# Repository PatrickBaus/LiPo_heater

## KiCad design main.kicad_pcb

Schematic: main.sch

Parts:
J1: USB_MICRO
J2, J3: Conn_01x02; JST_PH_B2B-PH-K_02x2.00mm_Straight
LOGO1: Logo_Open_Hardware_Small; OSHW-Logo_7.5x8mm_SilkScreen
Q1: DMP1045U; SOT-23
R1: 10k; R_0603_1608Metric

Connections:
/BAT+: J2.1; also elsewhere on the board
/Microcontroller/~enable_heater: Q1.1, R1.2; also elsewhere on the board
/Power Supply/V+5: Q1.2, R1.1; also elsewhere on the board
/Power Supply/VUSB: J1.1; also elsewhere on the board
GND: J1.5, J1.6, J2.2, J3.2; also elsewhere on the board
unnamed: J3.1, Q1.3

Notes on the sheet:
Heater

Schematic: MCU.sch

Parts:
C10, C11, C12: 100n; C_0603_1608Metric
J6: Conn_01x02; JST_PH_B2B-PH-K_02x2.00mm_Straight
J7: AVR-ISP-6; PinHeader_2x03_P2.54mm_Vertical
Q3: MMBT3904; SOT-23
R13: 1k; R_0603_1608Metric
R14, R17, R18: 4.7k; R_0603_1608Metric
R15: 470; R_0603_1608Metric
R16: 10k; R_0603_1608Metric
SW2: SW_SPDT; SW_CuK_OS102011MA1QN1_SPDT_Angled
U4: ATtiny13-20SSU; SOIC-8_3.9x4.9mm_P1.27mm

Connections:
/BAT+: R13.2; also elsewhere on the board
/Microcontroller/MISO: J7.1, R18.2, U4.6 (PB1)
/Microcontroller/MOSI: J7.4, R17.2, U4.5 (PB0)
/Microcontroller/RST: J7.5, R16.2, U4.1 (~RESET~/PB5)
/Microcontroller/SCK: J7.3, R14.2, U4.7 (PB2)
/Microcontroller/~enable_heater: U4.2 (PB3); also elsewhere on the board
/Power Supply/V+5: C10.1, J7.2, R15.1, R16.1, U4.8 (VCC); also elsewhere on the board
/Power Supply/~Kill_power: R17.1; also elsewhere on the board
GND: C10.2, C11.2, C12.2, J7.6, Q3.2 (E), SW2.1, U4.4 (GND); also elsewhere on the board
unnamed: C11.1, R13.1, U4.3 (PB4)
unnamed: C12.1, R14.1, SW2.2
unnamed: J6.1, R15.2
unnamed: J6.2, Q3.3 (C)
unnamed: Q3.1 (B), R18.1

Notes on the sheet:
To program the arduino. Connect the following wires: GND -> Pin 6 CTS -> Not Connected 5V/3.3V -> Pin 2 TXD ->
We are using a transistor so that we can isolate the pin using a 4.7k resistor

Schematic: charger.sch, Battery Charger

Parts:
C1, C2: 10u; C_0805_2012Metric
D1: Red LED; LED_0805_2012Metric
D2: Green LED; LED_0805_2012Metric
R2: 470; R_0603_1608Metric
R3: 1k; R_0603_1608Metric
R4: 2k; R_0603_1608Metric
U1: MCP73831; SOT-23-5

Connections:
/BAT+: C2.1, U1.3; also elsewhere on the board
/Power Supply/VUSB: C1.1, R2.2, U1.4; also elsewhere on the board
GND: C1.2, C2.2, R3.1, R4.1, U1.2; also elsewhere on the board
unnamed: D1.1, D2.2, U1.1
unnamed: D1.2, R2.1
unnamed: D2.1, R3.2
unnamed: R4.2, U1.5

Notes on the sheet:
Turns on, when fully charged
Turns on, when the charger is connected

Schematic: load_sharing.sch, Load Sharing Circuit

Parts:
Q2: NTLJF3117P; DFN-6-2EP_2x2mm_Pitch0.65mm
R5: 100k; R_0603_1608Metric

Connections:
/BAT+: Q2.3, Q2.8; also elsewhere on the board
/Power Supply/DC/DC boost converter/Vsup: Q2.4, Q2.6, Q2.7; also elsewhere on the board
/Power Supply/VUSB: Q2.1, Q2.5, R5.1; also elsewhere on the board
GND: R5.2; also elsewhere on the board

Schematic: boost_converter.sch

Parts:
C3: 10n; C_0603_1608Metric
C4, C8, C9: 47u; C_0805_2012Metric
C5: 100n; C_0603_1608Metric
C6: 200p; C_0603_1608Metric
C7: 18p; C_0603_1608Metric
D3: LED; LED_0805_2012Metric
JP1, JP2: SolderJumper_2_Open; SolderJumper-2_P1.3mm_Open_RoundedPad1.0x1.5mm
L1: 22u; Coilcraft_MSS7341
R6, R19: 1k; R_0603_1608Metric
R7: 100k; R_0603_1608Metric
R8: 332k; R_0603_1608Metric
R9: 33k; R_0603_1608Metric
R10: 150k; R_0603_1608Metric
R11: 22.6k; R_0603_1608Metric
R12: 1.1M; R_0603_1608Metric
SW1: SW_Push; SW_Tactile_SPST_Angled_PTS645Vx31-2LFS
TP1: Test_Point; TestPoint_Pad_D1.5mm
U2: LTC2955-1(DFN); DFN-10-1EP_2x3mm_P0.5mm_EP0.64x2.4mm
U3: LTC3536; DFN-10-1EP_3x3mm_P0.5mm_EP1.55x2.48mm

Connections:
/Power Supply/DC/DC boost converter/Vsup: C4.1, JP1.1, R6.1, U3.7; also elsewhere on the board
/Power Supply/V+5: C8.1, C9.1, JP2.1, R11.1, R12.1, R19.1, TP1.1, U3.6; also elsewhere on the board
/Power Supply/~Kill_power: JP2.2, U2.9; also elsewhere on the board
GND: C3.2, C4.2, C5.2, C8.2, C9.2, D3.1, R7.2, R8.2, R10.2, SW1.1, U2.6, U2.7, U2.10, U3.2, U3.3, U3.11; also elsewhere on the board
unnamed: C3.1, R6.2, U2.4
unnamed: C5.1, U2.8
unnamed: C6.1, R9.1
unnamed: C6.2, C7.2, R10.1, R12.2, U3.9
unnamed: C7.1, R11.2
unnamed: D3.2, R19.2
unnamed: JP1.2, R7.1, U2.3, U3.8
unnamed: L1.1, U3.4
unnamed: L1.2, U3.5
unnamed: R8.1, U3.1
unnamed: R9.2, U3.10
unnamed: SW1.2, U2.5

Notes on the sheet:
5.2 seconds/μF + 64 ms until forced shutdown
332 kΩ ≜ 300 kHz
Optional: Close JP1 for debugging to always enable the DC/DC converter
Optional: Close JP2 for debugging to keep the DC/DC converter enabled
The LTC2955 requires only 1.2 µA of current so the 1k resistor is OK and it allows reverse input.

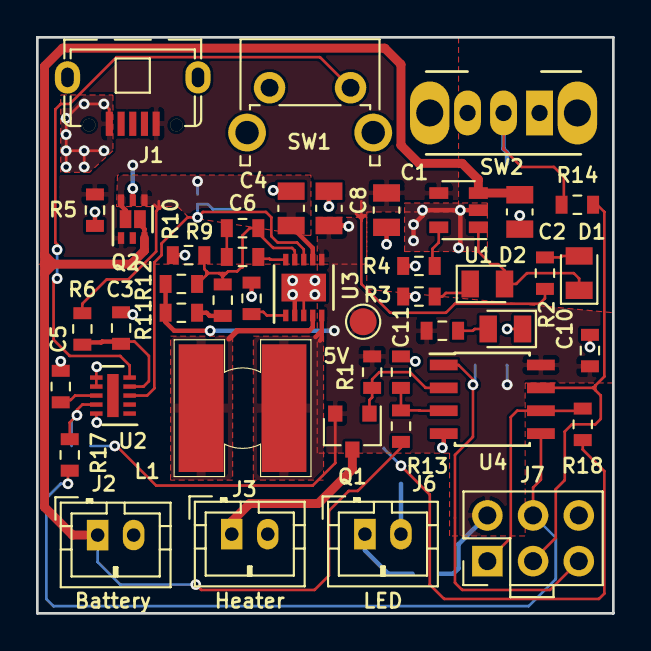
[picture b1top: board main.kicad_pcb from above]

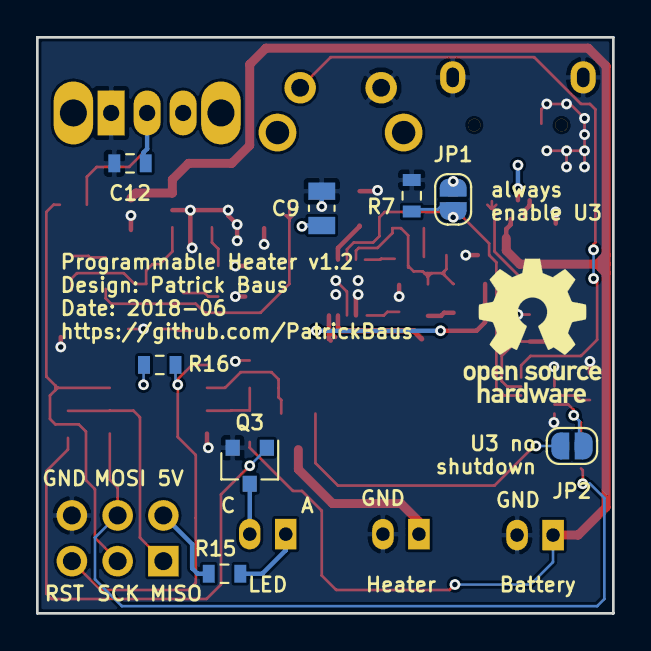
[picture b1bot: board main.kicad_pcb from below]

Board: 2 copper layers, 32.0 x 32.0 mm, 53 parts (9 on the bottom side), 33 nets.

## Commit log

2017-10-02 Cleanup and added .gitignore file
2017-10-02 Moved image to own folder
2017-10-02 cleanup
2017-10-31 Fixed NTLJF3117P MOSFET pin layout
2017-12-30 Moved MCU pins around to make sure that they do not interfere with the programmer Moved ISP Header closer to the edge of the board to allow easier access with the programmer Added pulldown resistor t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
2017-12-30 Added part names and BOM Added Gerber files
2018-03-19 Preparing for v1.2 Updated to KiCAD 5 nightly Added resistors to isolate the programming pins Added transistor to drive the LED Replaced LTC3458 boost converter with an LTC3536 buck-boost converter t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
2018-05-24 Updated to Kicad v5.0
2018-05-24 Added Gerber files v1.2
2018-05-24 Cleaned up datasheets
2018-05-24 Cleaned up symbols
2018-06-10 Added power on state LED Updated to KiCAD 5.0
2018-06-10 Added part numbers Updated BOM
2018-06-10 Updated libraries
2018-06-16 Changed description of the blue LED
